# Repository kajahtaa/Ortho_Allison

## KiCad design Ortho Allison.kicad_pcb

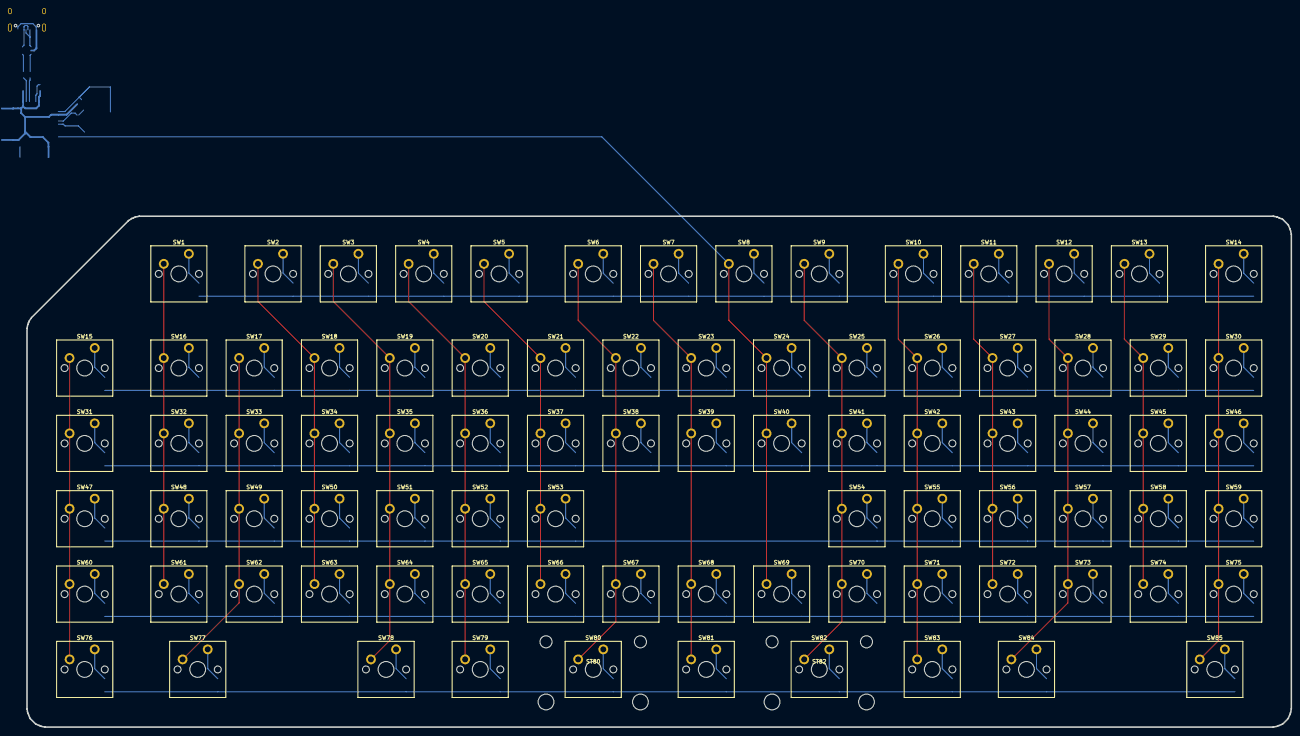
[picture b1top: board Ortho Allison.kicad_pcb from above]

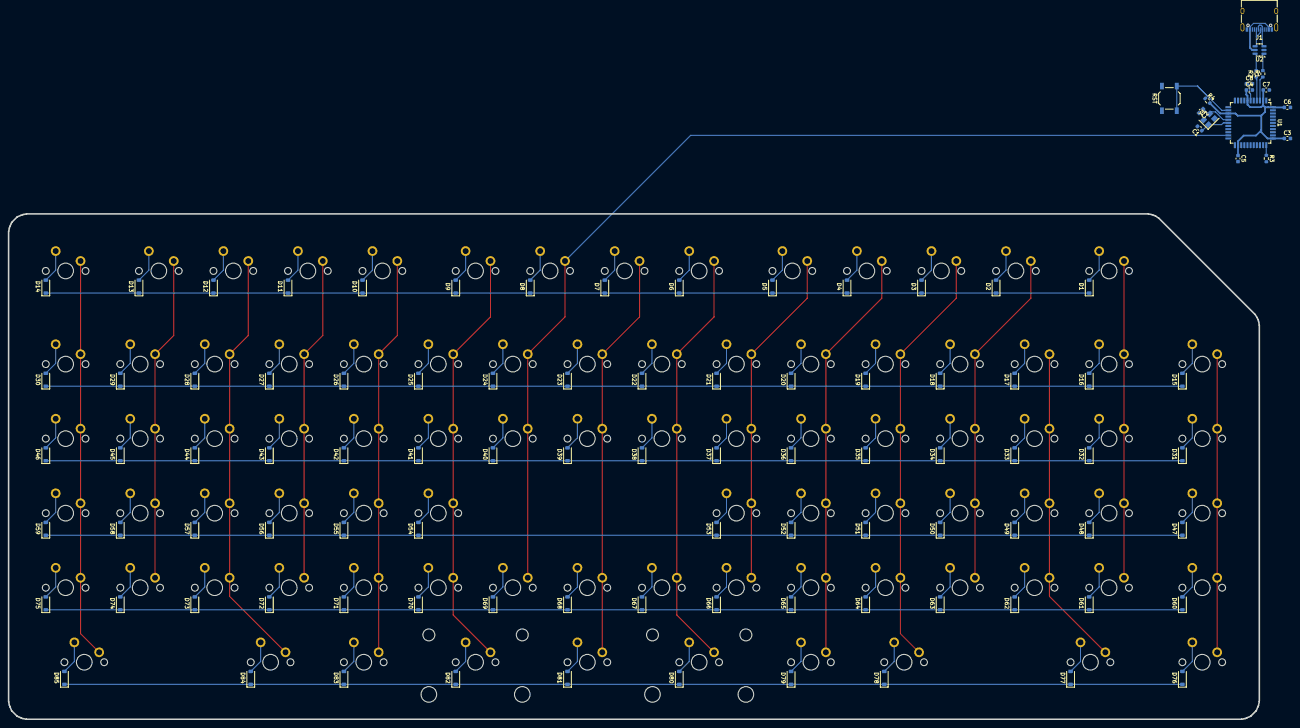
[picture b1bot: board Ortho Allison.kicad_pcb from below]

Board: 2 copper layers, 319.7 x 129.2 mm, 189 parts (102 on the bottom side), 120 nets.

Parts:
C1, C2: 22p; C_0603_1608Metric
C3, C4, C5, C6: 0.1u; C_0603_1608Metric
C7: 4.7u; C_0603_1608Metric
C8: 1u; C_0603_1608Metric
D1, D2, D3, D4, D5, D6, D7, D8, D9, D10, D11, D12, D13, D14, D15, D16, D17, D18, D19, D20, D21, D22, D23, D24, D25, D26, D27, D28, D29, D30, D31, D32, D33, D34, D35, D36, D37, D38, D39, D40, D41, D42, D43, D44, D45, D46, D47, D48, D49, D50, D51, D52, D53, D54, D55, D56, D57, D58, D59, D60, D61, D62, D63, D64, D65, D66, D67, D68, D69, D70, D71, D72, D73, D74, D75, D76, D77, D78, D79, D80, D81, D82, D83, D84, D85: D; D_SOD-123
J1: USB_C_Receptacle_USB2.0; USB_C_Receptacle_XKB_U262-16XN-4BVC11
R1, R2: 22; R_0603_1608Metric
R3, R4: 10k; R_0603_1608Metric
RST: SW_SPST; SW_SPST_TL3342
ST80, ST82: MountingHole; Stabilizer_Cherry_MX_2.00u
SW1, SW2, SW3, SW4, SW5, SW6, SW7, SW8, SW9, SW10, SW11, SW12, SW13, SW14, SW15, SW16, SW17, SW18, SW19, SW20, SW21, SW22, SW23, SW24, SW25, SW26, SW27, SW28, SW29, SW30, SW31, SW32, SW33, SW34, SW35, SW36, SW37, SW38, SW39, SW40, SW41, SW42, SW43, SW44, SW45, SW46, SW47, SW48, SW49, SW50, SW51, SW52, SW53, SW54, SW55, SW56, SW57, SW58, SW59, SW60, SW61, SW62, SW63, SW64, SW65, SW66, SW67, SW68, SW69, SW70, SW71, SW72, SW73, SW74, SW75, SW76, SW79, SW81, SW83: SW_Push; SW_Cherry_MX_PCB_1.00u
SW77, SW78, SW84, SW85: SW_Push; SW_Cherry_MX_PCB_1.50u
SW80, SW82: SW_Push; SW_Cherry_MX_PCB_2.00u
U1: ATmega32U4-A; TQFP-44_10x10mm_P0.8mm
U2: TPD2S017; SOT-23-6
Y1: Crystal_GND24; Crystal_SMD_3225-4Pin_3.2x2.5mm

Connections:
COL0: SW15.1, SW31.1, SW47.1, SW60.1, SW76.1, U1.39
COL1: SW1.1, SW16.1, SW32.1, SW48.1, SW61.1, U1.30
COL2: SW17.1, SW33.1, SW49.1, SW62.1, SW77.1, U1.38
COL3: SW2.1, SW18.1, SW34.1, SW50.1, SW63.1, U1.12
COL4: SW3.1, SW19.1, SW35.1, SW51.1, SW64.1, SW78.1, U1.31
COL5: SW4.1, SW20.1, SW36.1, SW52.1, SW65.1, SW79.1, U1.32
COL6: SW5.1, SW21.1, SW37.1, SW53.1, SW66.1, U1.18
COL7: SW6.1, SW22.1, SW38.1, SW67.1, SW80.1, U1.19
COL8: SW7.1, SW23.1, SW39.1, SW68.1, SW81.1, U1.20
COL9: SW8.1, SW24.1, SW40.1, SW69.1, U1.21
COL10: SW9.1, SW25.1, SW41.1, SW54.1, SW70.1, SW82.1, U1.25
COL11: SW10.1, SW26.1, SW42.1, SW55.1, SW71.1, SW83.1, U1.22
COL12: SW11.1, SW27.1, SW43.1, SW56.1, SW72.1, U1.26
COL13: SW12.1, SW28.1, SW44.1, SW57.1, SW73.1, SW84.1, U1.27
COL14: SW13.1, SW29.1, SW45.1, SW58.1, SW74.1, U1.41
COL15: SW14.1, SW30.1, SW46.1, SW59.1, SW75.1, SW85.1, U1.40
GND: C1.2, C2.2, C3.2, C4.2, C5.2, C6.2, C7.2, C8.2, J1.A1, J1.A12, J1.B1, J1.B12, J1.S1, R3.2, RST.1, U1.5, U1.15, U1.23, U1.35, U1.43, U2.2, Y1.2, Y1.4
unnamed: D1.2, SW1.2
unnamed: D2.2, SW2.2
unnamed: D3.2, SW3.2
unnamed: D4.2, SW4.2
unnamed: D5.2, SW5.2
unnamed: D6.2, SW6.2
unnamed: D7.2, SW7.2
unnamed: D8.2, SW8.2
unnamed: D9.2, SW9.2
unnamed: D10.2, SW10.2
unnamed: D11.2, SW11.2
unnamed: D12.2, SW12.2
unnamed: D13.2, SW13.2
unnamed: D14.2, SW14.2
unnamed: D15.2, SW15.2
unnamed: D16.2, SW16.2
unnamed: D17.2, SW17.2
unnamed: D18.2, SW18.2
unnamed: D19.2, SW19.2
unnamed: D20.2, SW20.2
unnamed: D21.2, SW21.2
unnamed: D22.2, SW22.2
unnamed: D23.2, SW23.2
unnamed: D24.2, SW24.2
unnamed: D25.2, SW25.2
unnamed: D26.2, SW26.2
unnamed: D27.2, SW27.2
unnamed: D28.2, SW28.2
unnamed: D29.2, SW29.2
unnamed: D30.2, SW30.2
unnamed: D31.2, SW31.2
unnamed: D32.2, SW32.2
unnamed: D33.2, SW33.2
unnamed: D34.2, SW34.2
unnamed: D35.2, SW35.2
unnamed: D36.2, SW36.2
unnamed: D37.2, SW37.2
unnamed: D38.2, SW38.2
unnamed: D39.2, SW39.2
unnamed: D40.2, SW40.2
unnamed: D41.2, SW41.2
unnamed: D42.2, SW42.2
unnamed: D43.2, SW43.2
unnamed: D44.2, SW44.2
unnamed: D45.2, SW45.2
unnamed: D46.2, SW46.2
unnamed: D47.2, SW47.2
unnamed: D48.2, SW48.2
unnamed: D49.2, SW49.2
unnamed: D50.2, SW50.2
unnamed: D51.2, SW51.2
unnamed: D52.2, SW52.2
unnamed: D53.2, SW53.2
unnamed: D54.2, SW54.2
unnamed: D55.2, SW55.2
unnamed: D56.2, SW56.2
unnamed: D57.2, SW57.2
unnamed: D58.2, SW58.2
unnamed: D59.2, SW59.2
unnamed: D60.2, SW60.2
unnamed: D61.2, SW61.2
unnamed: D62.2, SW62.2
unnamed: D63.2, SW63.2
unnamed: D64.2, SW64.2
unnamed: D65.2, SW65.2
unnamed: D66.2, SW66.2
unnamed: D67.2, SW67.2
unnamed: D68.2, SW68.2
unnamed: D69.2, SW69.2
unnamed: D70.2, SW70.2
unnamed: D71.2, SW71.2
unnamed: D72.2, SW72.2
unnamed: D73.2, SW73.2
unnamed: D74.2, SW74.2
unnamed: D75.2, SW75.2
unnamed: D76.2, SW76.2
unnamed: D77.2, SW77.2
unnamed: D78.2, SW78.2
unnamed: D79.2, SW79.2
unnamed: D80.2, SW80.2
unnamed: D81.2, SW81.2
unnamed: D82.2, SW82.2
unnamed: D83.2, SW83.2
unnamed: D84.2, SW84.2
unnamed: D85.2, SW85.2
ROW0: D1.1, D2.1, D3.1, D4.1, D5.1, D6.1, D7.1, D8.1, D9.1, D10.1, D11.1, D12.1, D13.1, D14.1, U1.8
ROW1: D15.1, D16.1, D17.1, D18.1, D19.1, D20.1, D21.1, D22.1, D23.1, D24.1, D25.1, D26.1, D27.1, D28.1, D29.1, D30.1, U1.9
ROW2: D31.1, D32.1, D33.1, D34.1, D35.1, D36.1, D37.1, D38.1, D39.1, D40.1, D41.1, D42.1, D43.1, D44.1, D45.1, D46.1, U1.10
ROW3: D47.1, D48.1, D49.1, D50.1, D51.1, D52.1, D53.1, D54.1, D55.1, D56.1, D57.1, D58.1, D59.1, U1.11
ROW4: D60.1, D61.1, D62.1, D63.1, D64.1, D65.1, D66.1, D67.1, D68.1, D69.1, D70.1, D71.1, D72.1, D73.1, D74.1, D75.1, U1.28
ROW5: D76.1, D77.1, D78.1, D79.1, D80.1, D81.1, D82.1, D83.1, D84.1, D85.1, U1.29
VCC: C3.1, C4.1, C5.1, C6.1, C7.1, J1.A4, J1.A9, J1.B4, J1.B9, R4.2, U1.2, U1.7, U1.14, U1.24, U1.34, U1.44, U2.5
mcu/D+: R2.1, U1.4
mcu/D-: R1.1, U1.3
mcu/UCAP: C8.1, U1.6
mcu/XTAL1: C1.1, U1.17, Y1.1
mcu/XTAL2: C2.1, U1.16, Y1.3
mcu/~HWB/PE2: R3.1, U1.33
mcu/~RESET: R4.1, RST.2, U1.13
u2/D+: R2.2, U2.6
u2/D-: R1.2, U2.1
usb/D+: J1.A6, J1.B6, U2.4
usb/D-: J1.A7, J1.B7, U2.3

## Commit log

2025-06-06 Add files via upload
    no idea if this is valid, based on some stuff i found in another github repo
    consult at your own risk
2025-06-06 Update Allison_KLE_v2.json
    typo correction
2025-06-06 testing
2025-06-06 built by keyboard-tools.xyz
    not a functional PCB but snazzy AF
